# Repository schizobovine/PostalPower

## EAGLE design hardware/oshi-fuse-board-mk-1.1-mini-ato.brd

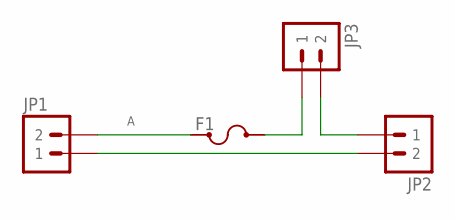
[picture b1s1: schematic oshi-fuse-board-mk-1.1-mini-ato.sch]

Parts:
F1: FUSEMINI-AUTO; KEYSTONE-MINI-AUTO-FUSE-HOLDER
JP1, JP2, JP3: M025MM; SCREWTERMINAL-5MM-2

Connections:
A: F1.P1@1 (1), F1.P1@2 (1), JP1.2
unnamed: JP1.1, JP2.2
unnamed: F1.P2@1 (2), F1.P2@2 (2), JP3.1
unnamed: JP2.1, JP3.2

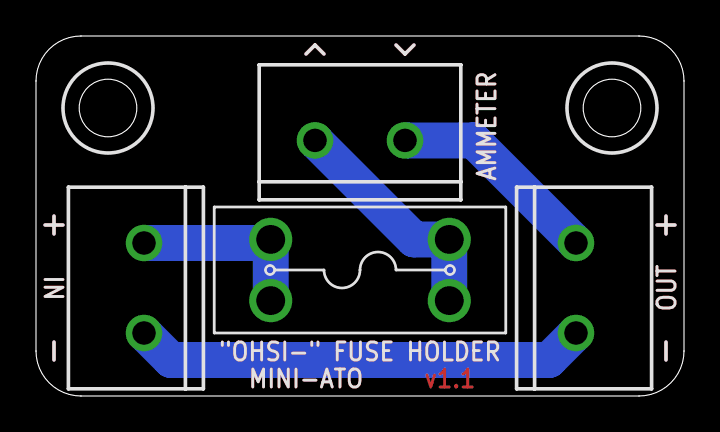
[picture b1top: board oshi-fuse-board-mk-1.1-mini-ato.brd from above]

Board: 2 copper layers, 36.0 x 20.0 mm, 4 parts (0 on the bottom side), 4 nets.

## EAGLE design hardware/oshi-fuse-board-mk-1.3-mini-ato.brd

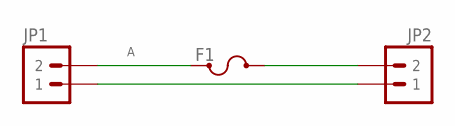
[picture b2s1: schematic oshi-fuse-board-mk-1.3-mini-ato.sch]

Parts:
F1: FUSEMINI-897; KEYSTONE-MINI-897-FUSE-HOLDER
JP1, JP2: M025MM; SCREWTERMINAL-5MM-2

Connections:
A: F1.P1@1 (1), F1.P1@2 (1), JP1.2
unnamed: F1.P2@1 (2), F1.P2@2 (2), JP2.2
unnamed: JP1.1, JP2.1

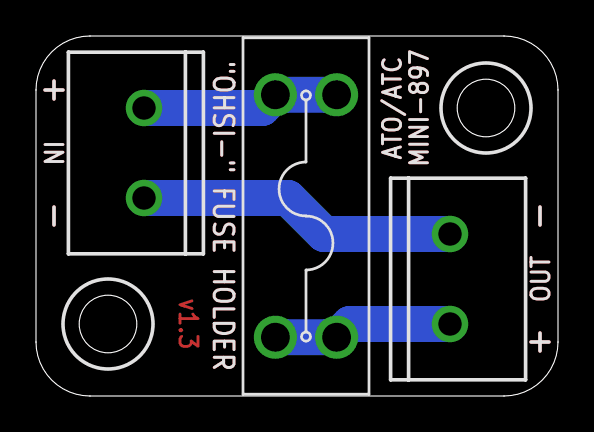
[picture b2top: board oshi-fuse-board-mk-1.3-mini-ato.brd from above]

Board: 2 copper layers, 29.0 x 20.0 mm, 3 parts (0 on the bottom side), 3 nets.

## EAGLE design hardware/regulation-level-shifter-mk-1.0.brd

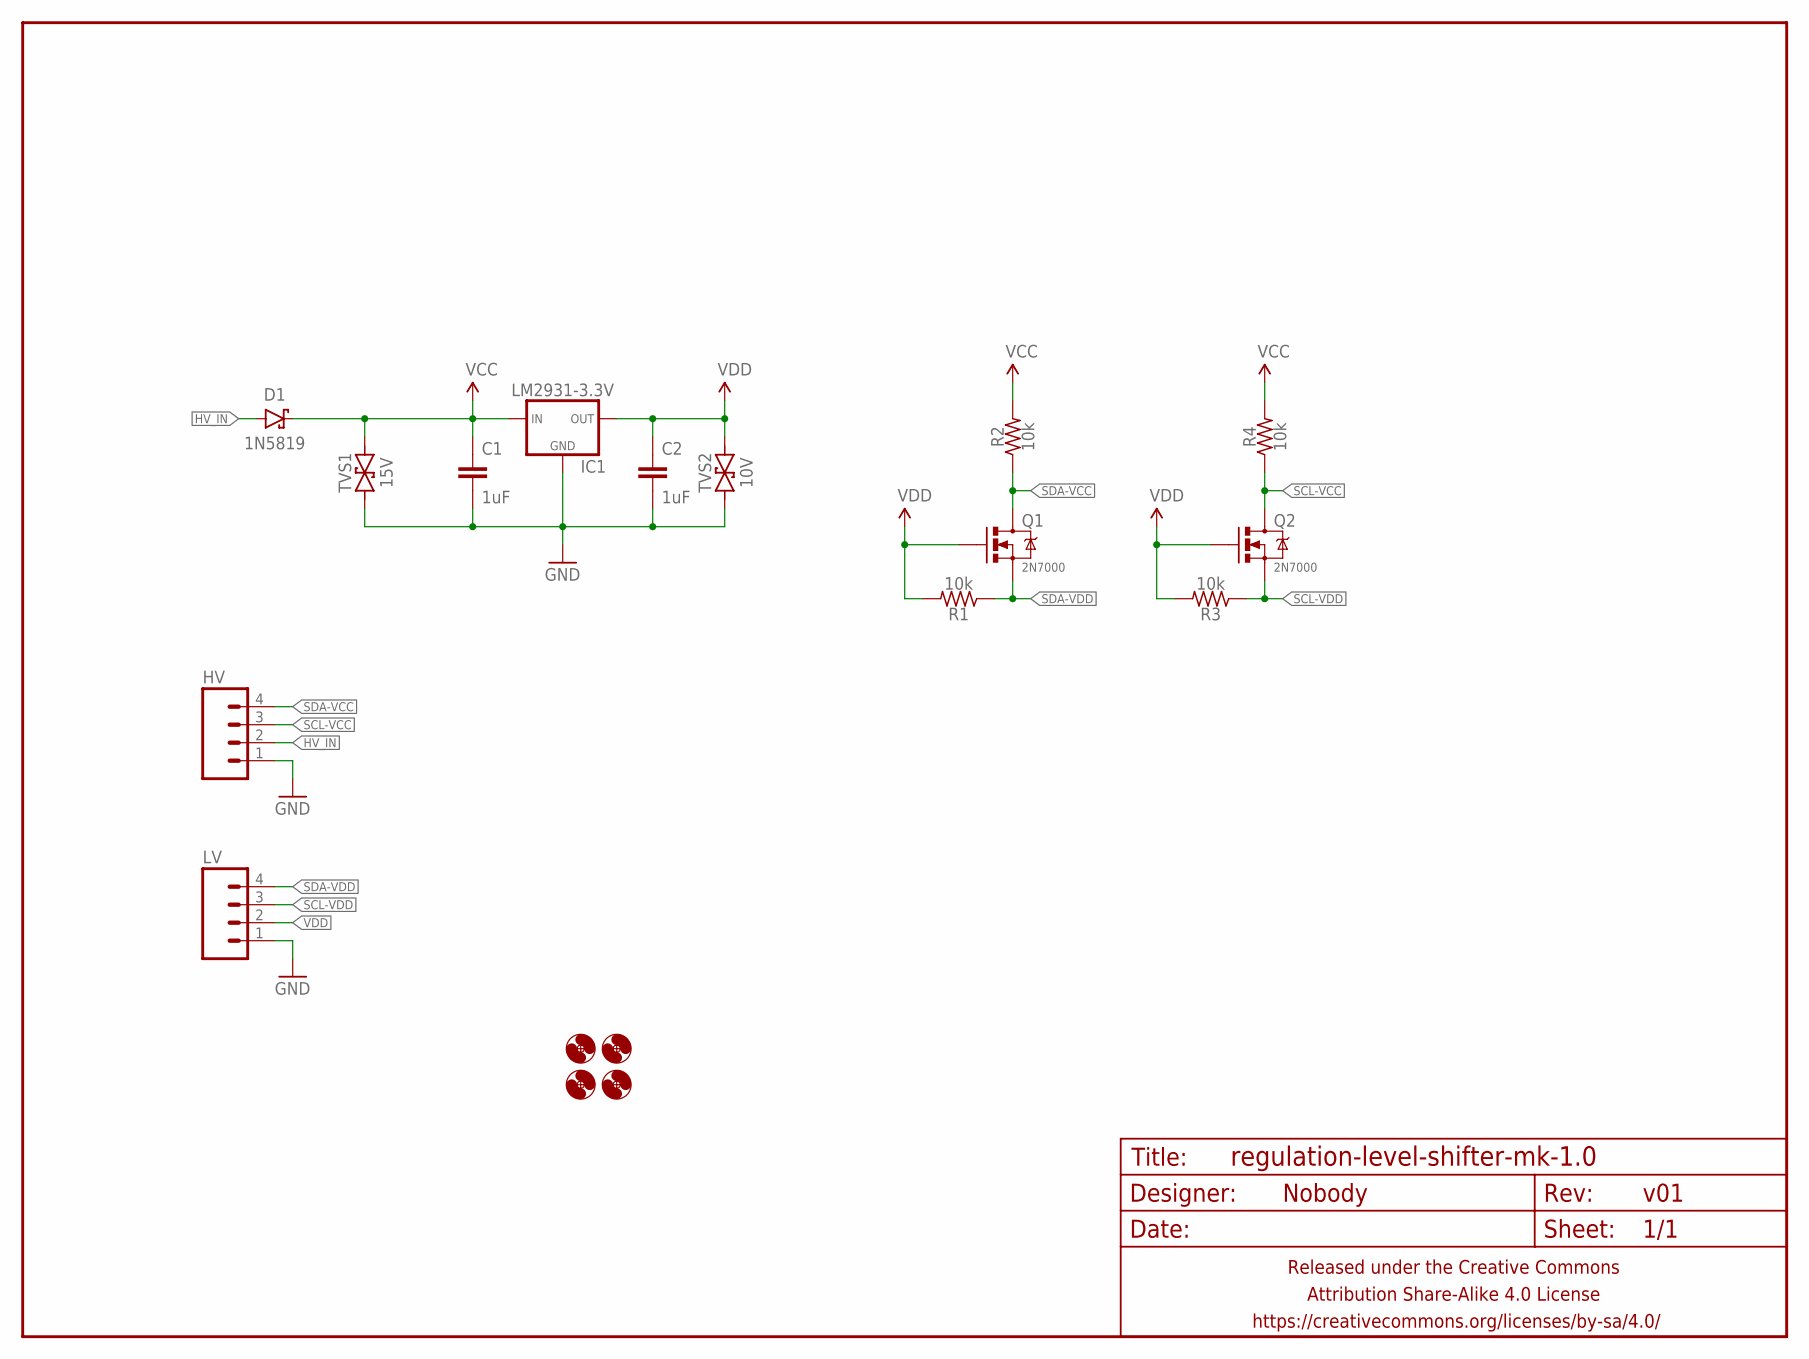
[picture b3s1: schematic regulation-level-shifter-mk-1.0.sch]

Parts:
C1, C2: 1uF; C025-024X044
D1: 1N5819; DIODE-10.16MM
FRAME1: FRAME-LETTERNO_PACKAGE; DUMMY
H1, H2, H3, H4: HOLE#2; HOLE-#2
HV: M04PTH; 1X04-PTH-VERT
IC1: LM2931-3.3V; TO-92-AMMO
LV: M04PTH; 1X04-PTH-VERT
Q1, Q2: 2N7000; TO-92-AMMO
R1, R2, R3, R4: 10k; RESISTOR-AXIAL-PTH-5.08MM
TVS1: 15V; DO-41-TVS-BI-10.16MM
TVS2: 10V; DO-41-TVS-BI-10.16MM

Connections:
GND: C1.2, C2.2, HV.1, IC1.2 (GND), LV.1, TVS1.P$1 (1), TVS2.P$1 (1)
HV_IN: D1.A, HV.2
SCL-VCC: HV.3, Q2.3 (D), R4.P$1 (1)
SCL-VDD: LV.3, Q2.1 (S), R3.P$1 (1)
SDA-VCC: HV.4, Q1.3 (D), R2.P$1 (1)
SDA-VDD: LV.4, Q1.1 (S), R1.P$1 (1)
VCC: C1.1, D1.C, IC1.1 (IN), R2.P$2 (2), R4.P$2 (2), TVS1.P$2 (2)
VDD: C2.1, IC1.3 (OUT), LV.2, Q1.2 (G), Q2.2 (G), R1.P$2 (2), R3.P$2 (2), TVS2.P$2 (2)

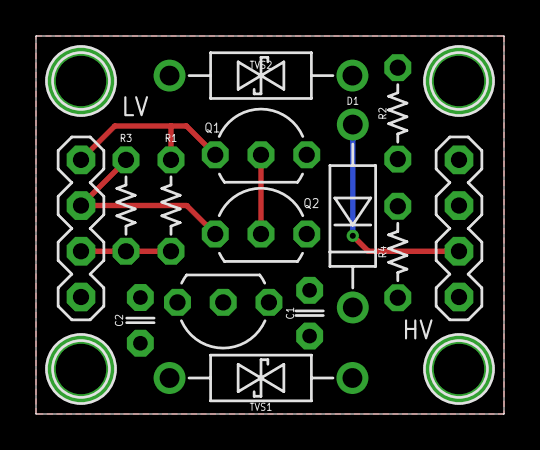
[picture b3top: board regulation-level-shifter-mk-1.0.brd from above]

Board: 2 copper layers, 26.0 x 21.0 mm, 19 parts (0 on the bottom side), 8 nets.

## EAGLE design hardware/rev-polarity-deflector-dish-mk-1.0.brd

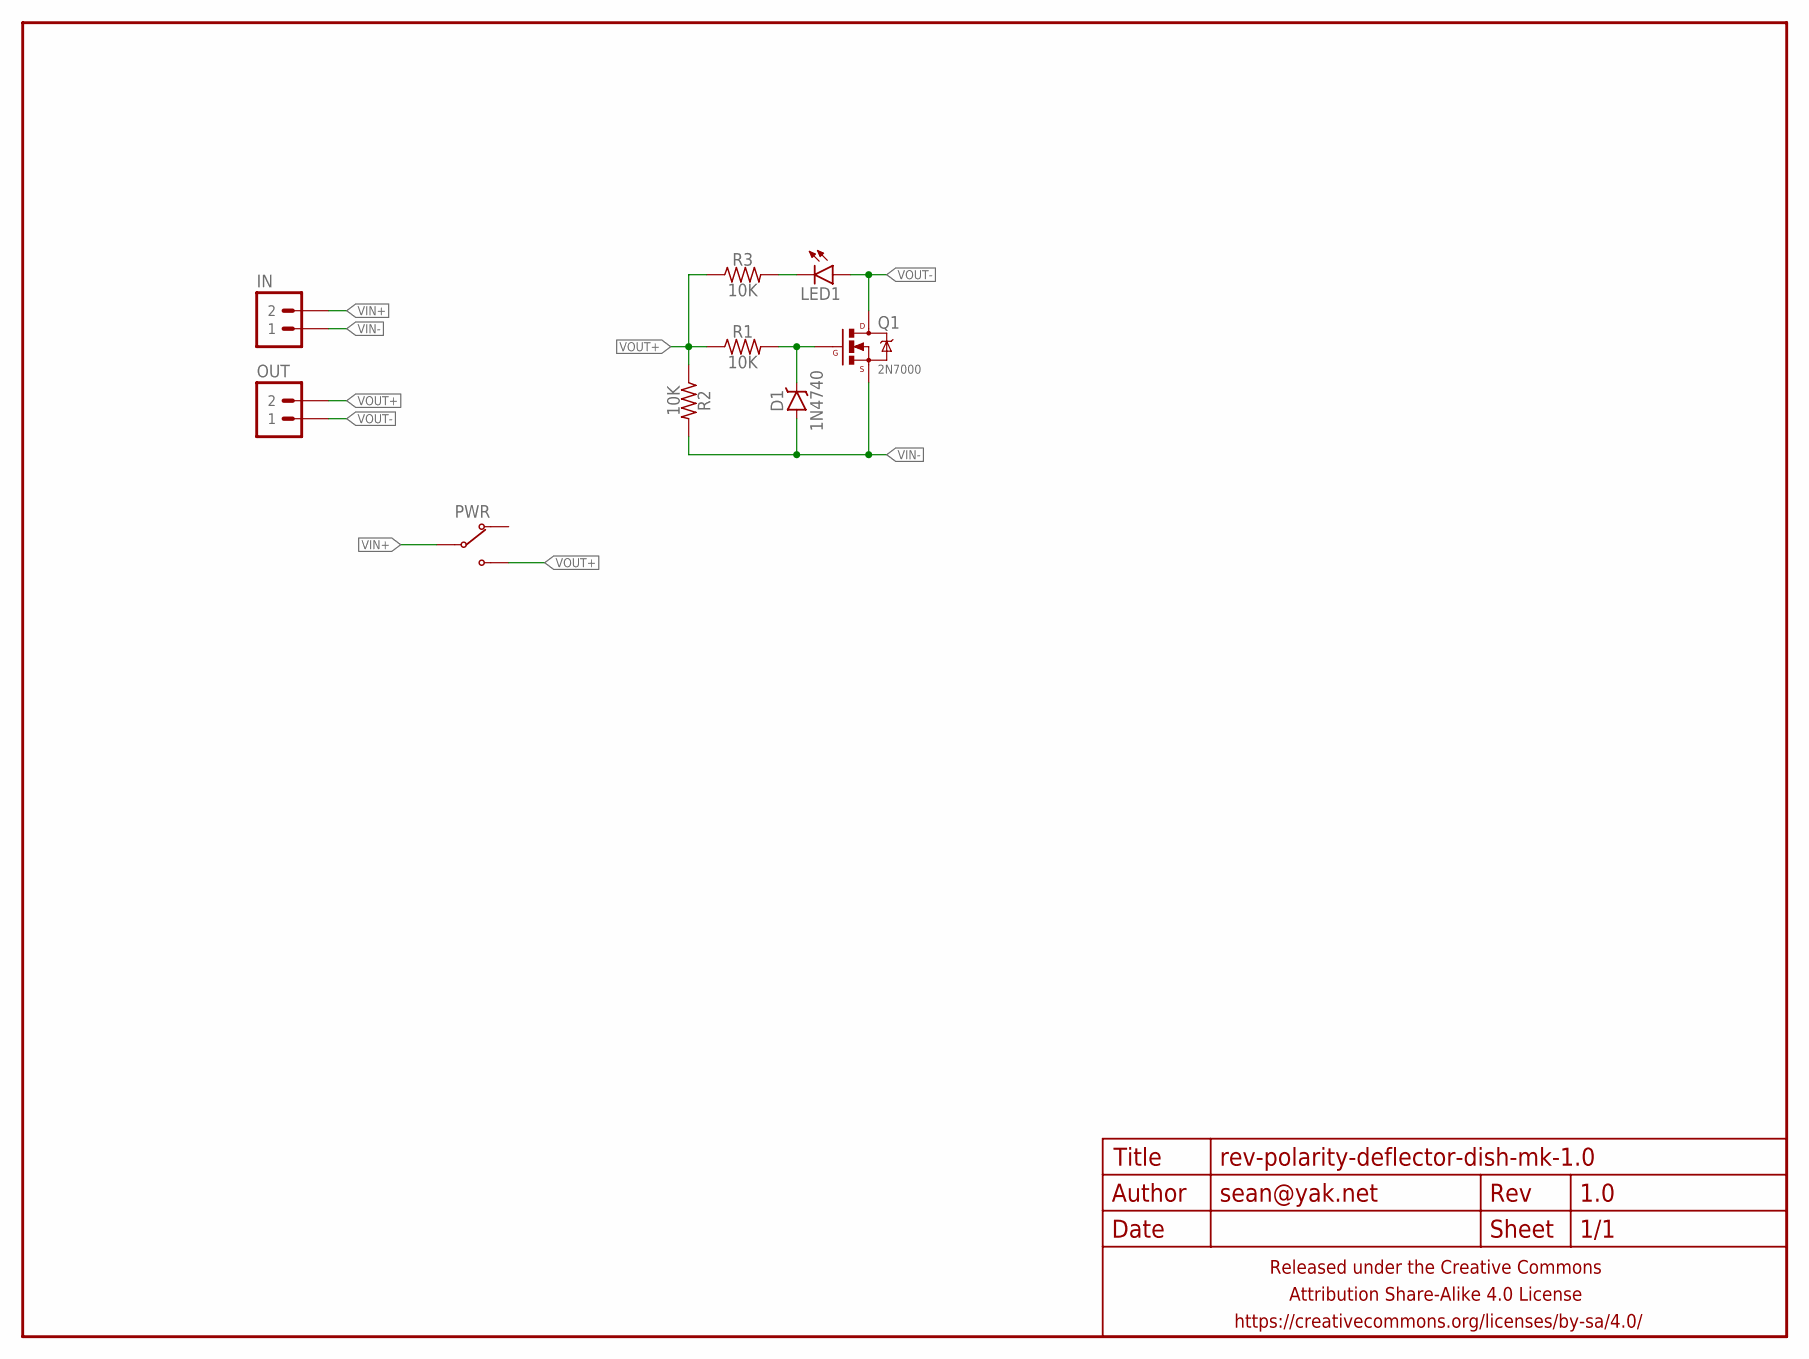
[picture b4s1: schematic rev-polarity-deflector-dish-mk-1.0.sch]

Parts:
D1: 1N4740; DIODE-ZENNER-7.62MM
FRAME1: FRAME-LETTERNO_PACKAGE; DUMMY
IN: M02PTH-CENTERED-R+; 1X02-CENTER-R+
LED1: LED3MM-LESS; LED3MM-LESSSILK
OUT: M02PTH-CENTERED-R+; 1X02-CENTER-R+
PWR: SWITCH-SPDTPTH-VERT-2.54MM; SWITCH-SPDT
Q1: 2N7000; TO-92-AMMO
R1, R2, R3: 10K; RESISTOR-AXIAL-PTH-7.62MM

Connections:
unnamed: D1.K (C), Q1.2 (G), R1.P$2 (2)
unnamed: LED1.K (C), R3.P$2 (2)
VIN+: IN.2, PWR.2 (COM)
VIN-: D1.A, IN.1, Q1.1 (S), R2.P$2 (2)
VOUT+: OUT.2, PWR.3 (NO), R1.P$1 (1), R2.P$1 (1), R3.P$1 (1)
VOUT-: LED1.A, OUT.1, Q1.3 (D)

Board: 2 copper layers, 10 parts (1 on the bottom side), 6 nets, no tracks yet.

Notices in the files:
parts and their libraries:
A_butts: Released under the Creative Commons Attribution Share-Alike 4.0 License
A_butts: https://creativecommons.org/licenses/by-sa/4.0
A_butts: Released under the Creative Commons
